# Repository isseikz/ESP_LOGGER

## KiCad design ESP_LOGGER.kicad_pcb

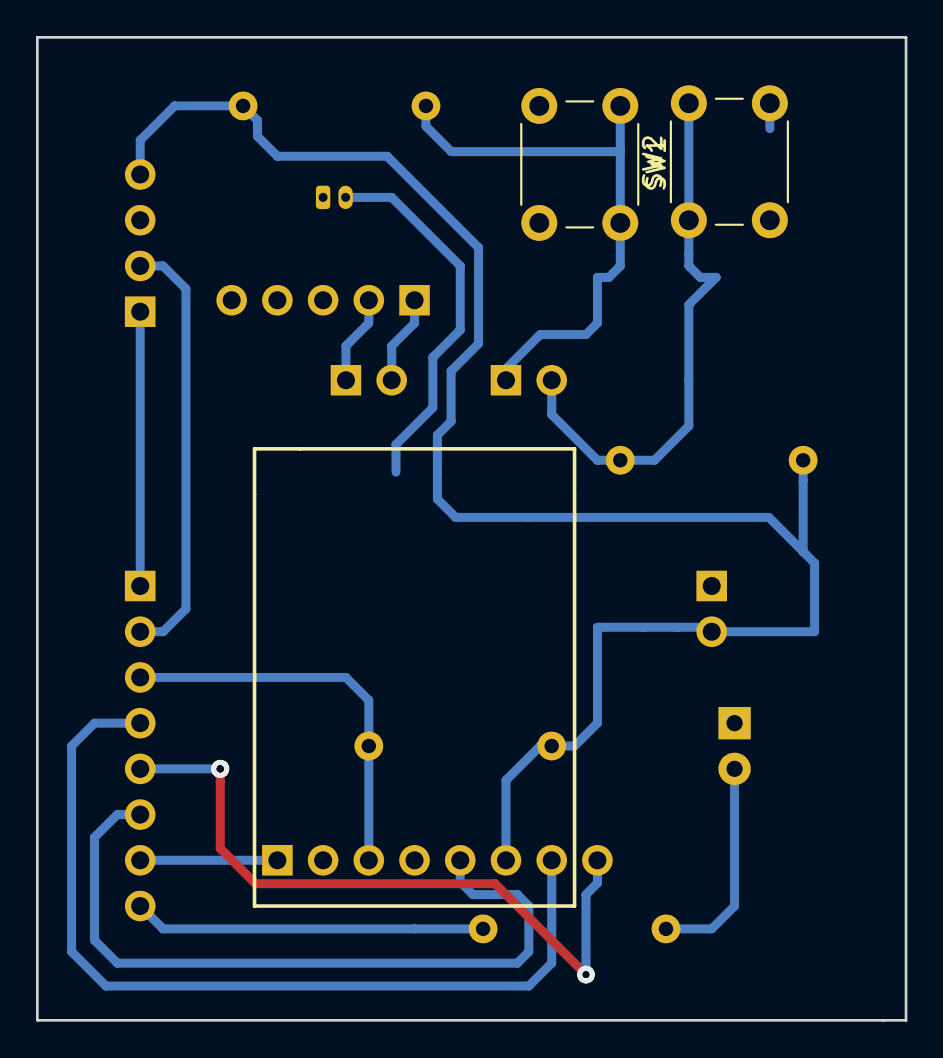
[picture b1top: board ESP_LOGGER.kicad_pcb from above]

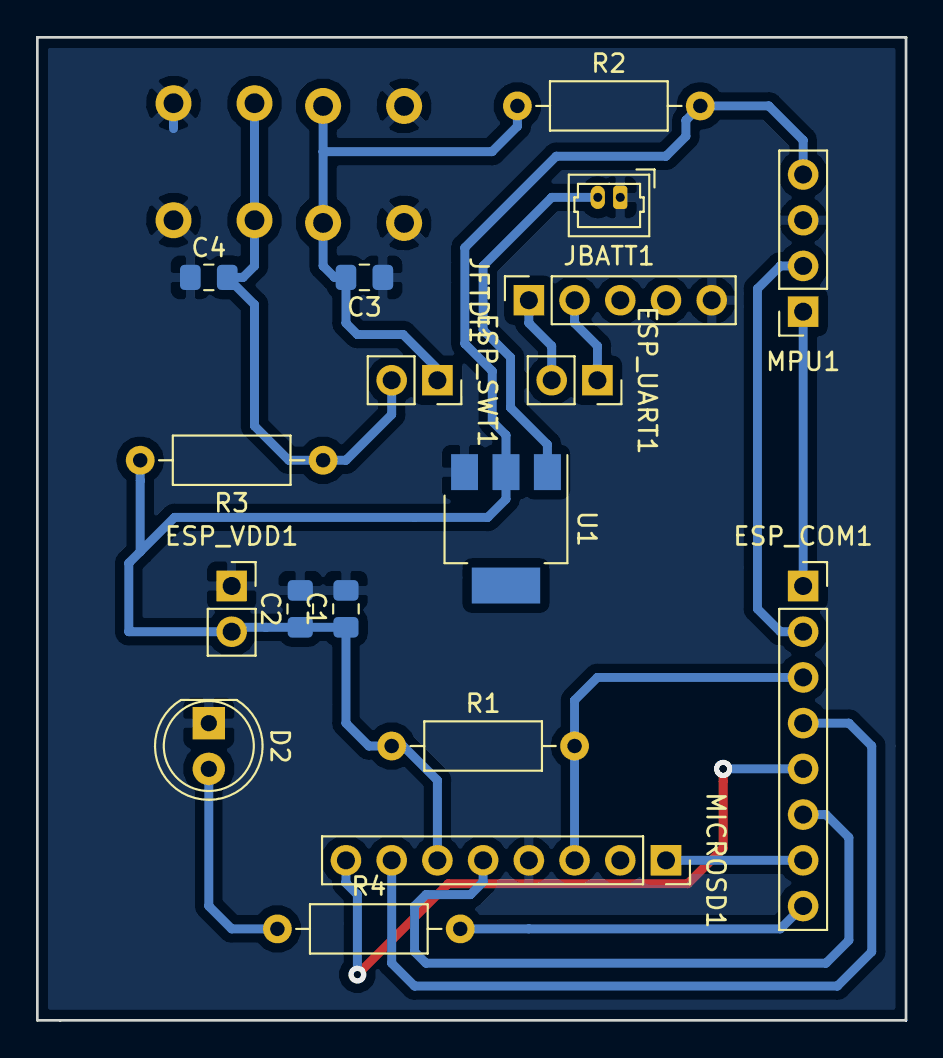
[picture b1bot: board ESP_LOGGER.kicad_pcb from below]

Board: 2 copper layers, 48.3 x 54.6 mm, 20 parts (18 on the bottom side), 16 nets.

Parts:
C1: 100u; C_0805_2012Metric_Pad1.15x1.40mm_HandSolder
C2: 1u; C_0805_2012Metric_Pad1.15x1.40mm_HandSolder
C3, C4: 1n; C_0805_2012Metric_Pad1.15x1.40mm_HandSolder
D2: LED; LED_D5.0mm_Clear
ESP_COM1: Conn_01x08_Female; PinSocket_1x08_P2.54mm_Vertical
ESP_SWT1: Conn_01x02_Female; PinSocket_1x02_P2.54mm_Vertical
ESP_UART1: Conn_01x02_Female; PinSocket_1x02_P2.54mm_Vertical
ESP_VDD1: Conn_01x02_Female; PinSocket_1x02_P2.54mm_Vertical
JBATT1: Conn_01x02_Female; Molex_PicoBlade_53047-0410_1x02_P1.25mm_Vertical
JFTDI1: Conn_01x05_Female; PinSocket_1x05_P2.54mm_Vertical
MICROSD1: Conn_01x08_Female; PinSocket_1x08_P2.54mm_Vertical
MPU1: Conn_01x04_Female; PinSocket_1x04_P2.54mm_Vertical
R1: R; R_Axial_DIN0207_L6.3mm_D2.5mm_P10.16mm_Horizontal
R2, R3: 10k; R_Axial_DIN0207_L6.3mm_D2.5mm_P10.16mm_Horizontal
R4: 1k; R_Axial_DIN0207_L6.3mm_D2.5mm_P10.16mm_Horizontal
SW1, SW2: SW_Push; SW_PUSH_6mm
U1: AZ1086_SOT223; SOT-223

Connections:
3.3V: C1.1, C2.1, ESP_VDD1.2, MICROSD1.6, MPU1.4, R1.1, R2.2, R3.2, U1.2
BATT: JBATT1.2, U1.1
BATT_GND: C1.2, C2.2, C3.1, C4.1, D2.1, ESP_VDD1.1, JBATT1.1, JFTDI1.5, MICROSD1.4, MPU1.3, SW1.2, SW2.2, U1.3
BOOT: C3.2, ESP_SWT1.1, R2.1, SW1.1
CD: ESP_COM1.7, MICROSD1.1
CS: ESP_COM1.5, MICROSD1.8
D0: ESP_COM1.3, MICROSD1.3, R1.2
DI: ESP_COM1.4, MICROSD1.7
EN: C4.2, ESP_SWT1.2, R3.1, SW2.1
IO_LED: ESP_COM1.8, R4.2
unnamed: D2.2, R4.1
PC_RX: ESP_UART1.2, JFTDI1.1
PC_TX: ESP_UART1.1, JFTDI1.2
SCK: ESP_COM1.6, MICROSD1.5
SCL: ESP_COM1.2, MPU1.2
SDA: ESP_COM1.1, MPU1.1

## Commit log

2018-10-16 schematic
2018-10-16 pcb F.Cu
2018-10-17 bugfix
2018-10-20 improvement in the size and usability
